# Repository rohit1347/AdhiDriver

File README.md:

# Mudroc
Motor driver based on VHN5019.

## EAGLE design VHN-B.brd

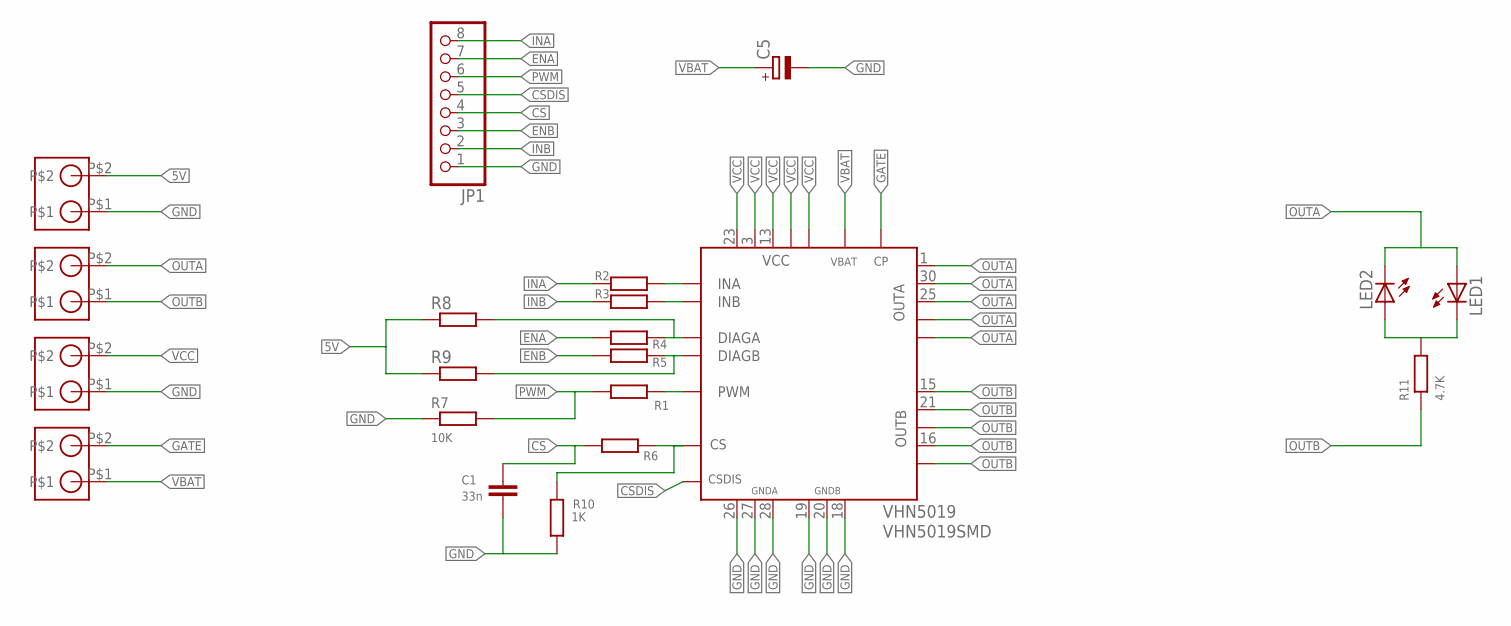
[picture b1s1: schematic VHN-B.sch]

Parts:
C1: 33n; C0402
C5: CPOL-EUE2,5-6E; E2,5-6E
JP1: PINHD-1X8; 1X08
LED1, LED2: LEDCHIPLED_0603; CHIPLED_0603
R1, R2, R3, R4, R5, R6, R8, R9: R-EU_R0402; R0402
R7: 10K; R0402
R10: 1K; R0402
R11: 4.7K; R0402
U$1, U$2, U$3, U$4: PBCON; 02P
VHN5019: VHN5019SMD; SO-30

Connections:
5V: R8.1, R9.1, U$4.P$2
CS: C1.1, JP1.4, R6.1
CSDIS: JP1.5, VHN5019.6 (CSDIS)
ENA: JP1.7, R4.1
ENB: JP1.3, R5.1
GATE: U$3.P$2, VHN5019.11 (CP)
GND: C1.2, C5.-, JP1.1, R7.1, R10.1, U$1.P$1, U$4.P$1, VHN5019.18 (GNDB), VHN5019.19 (GNDB), VHN5019.20 (GNDB), VHN5019.26 (GNDA), VHN5019.27 (GNDA), VHN5019.28 (GNDA)
INA: JP1.8, R2.1
INB: JP1.2, R3.1
unnamed: R2.2, VHN5019.4 (INA)
unnamed: R3.2, VHN5019.10 (INB)
unnamed: R4.2, R8.2, VHN5019.5 (DIAGA)
unnamed: R5.2, R9.2, VHN5019.9 (DIAGB)
unnamed: R1.2, VHN5019.7 (PWM)
unnamed: LED1.C, LED2.A, R11.2
unnamed: R6.2, R10.2, VHN5019.8 (CS)
OUTA: LED1.A, LED2.C, U$2.P$2, VHN5019.1 (OUTA), VHN5019.25 (OUTA), VHN5019.30 (OUTA), VHN5019.OUTA, VHN5019.OUTA@1 (OUTA)
OUTB: R11.1, U$2.P$1, VHN5019.15 (OUTB), VHN5019.16 (OUTB), VHN5019.21 (OUTB), VHN5019.OUTB, VHN5019.OUTB@1 (OUTB)
PWM: JP1.6, R1.1, R7.2
VBAT: C5.+, U$3.P$1, VHN5019.12 (VBAT)
VCC: U$1.P$2, VHN5019.3 (VCC), VHN5019.13 (VCC), VHN5019.23 (VCC), VHN5019.VCC, VHN5019.VCC@1 (VCC)

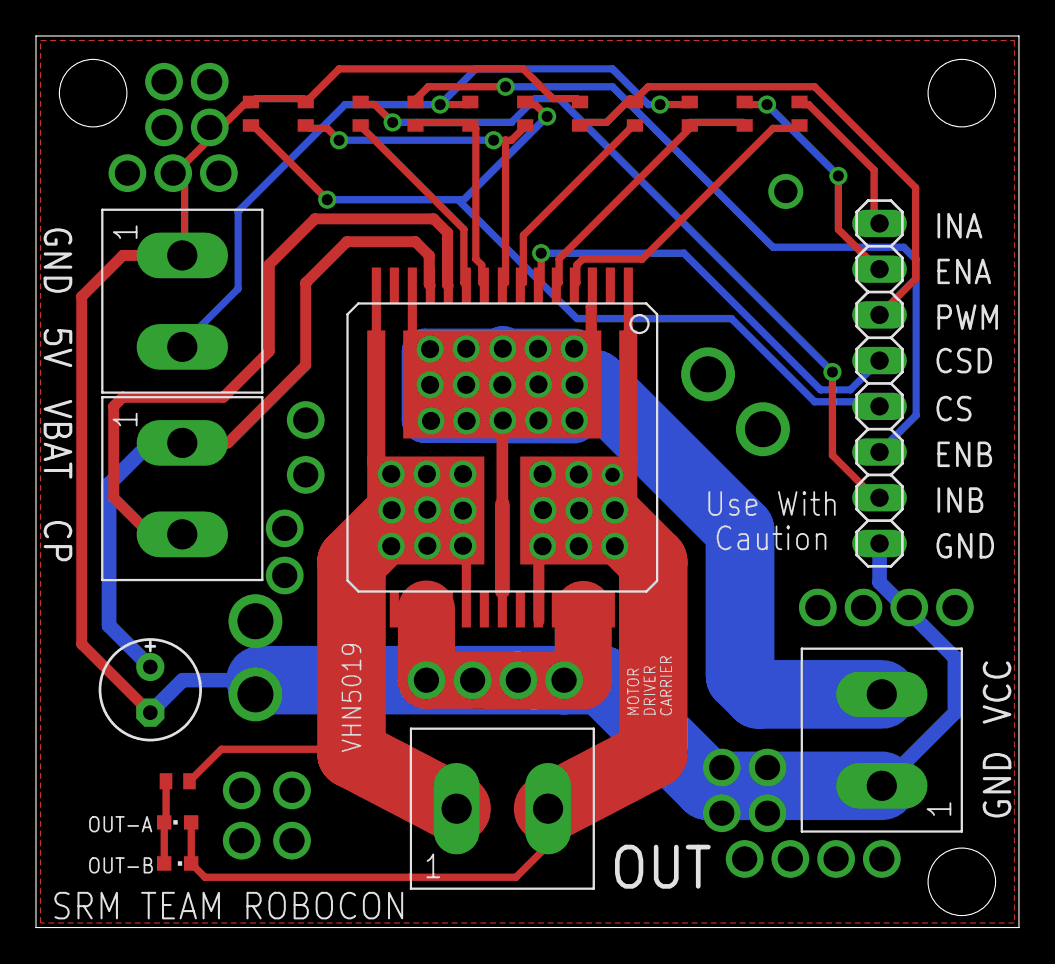
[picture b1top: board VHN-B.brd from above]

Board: 2 copper layers, 54.6 x 49.5 mm, 21 parts (0 on the bottom side), 21 nets.
